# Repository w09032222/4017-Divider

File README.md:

# 4017-Divider

A simple 2hp clock divider module inspired by the 4017 ic.

Input a clock signal and the other 7 outputs will send out signals which dividing the input's frequency by 2 to 8.

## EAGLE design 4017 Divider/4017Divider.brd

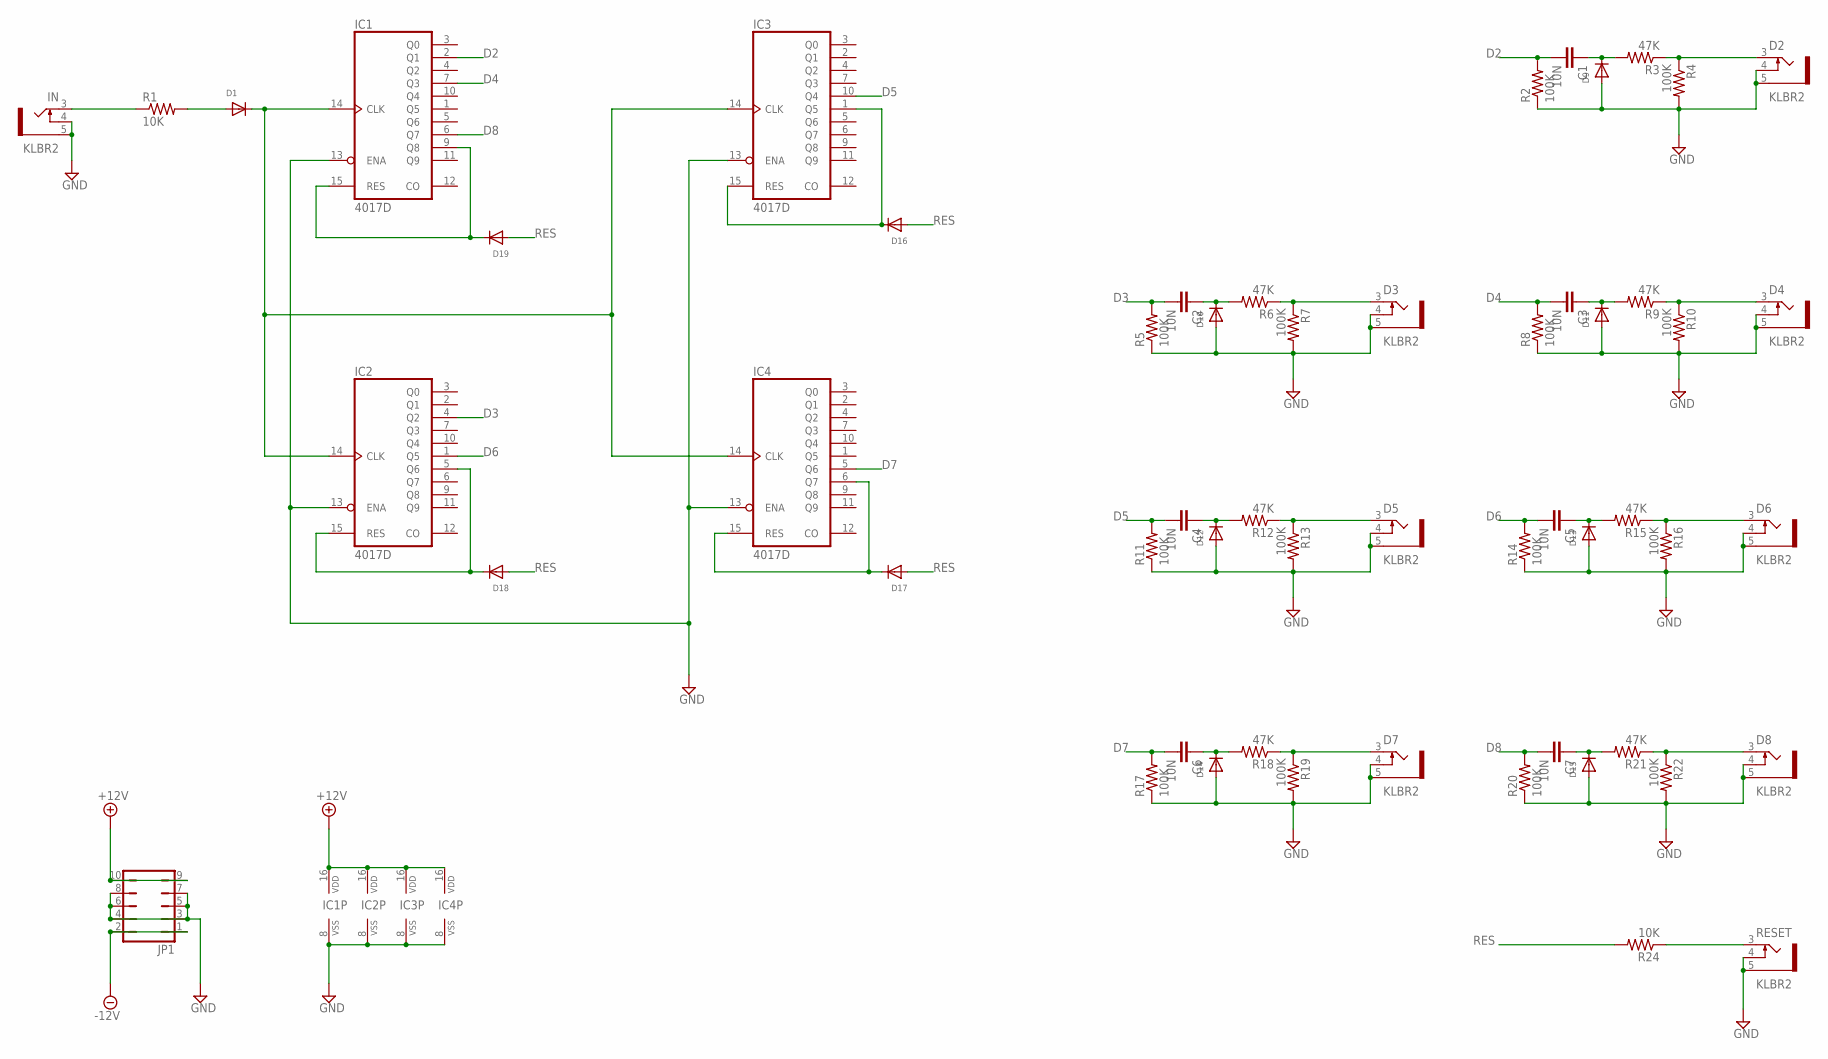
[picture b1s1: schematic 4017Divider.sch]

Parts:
C1, C2, C3, C4, C5, C6, C7: 10N; C0603K
D1, D9, D10, D11, D12, D13, D14, D15, D16, D17, D18, D19: DIODESOD-123; SOD-123
D2, D3, D4, D5, D6, D7, D8: KLBR2
IC1, IC2, IC3, IC4: 4017D; SO16
IN: KLBR2
JP1: JP5Q
R1, R24: 10K; R0603
R2, R4, R5, R7, R8, R10, R11, R13, R14, R16, R17, R19, R20, R22: 100K; R0603
R3, R6, R9, R12, R15, R18, R21: 47K; R0603
RESET: KLBR2

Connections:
+12V: IC1.16 (VDD), IC2.16 (VDD), IC3.16 (VDD), IC4.16 (VDD), JP1.9, JP1.10
-12V: JP1.1, JP1.2
D2: C1.2, IC1.2 (Q1), R2.2
D3: C2.2, IC2.4 (Q2), R5.2
D4: C3.2, IC1.7 (Q3), R8.2
D5: C4.2, IC3.10 (Q4), R11.2
D6: C5.2, IC2.1 (Q5), R14.2
D7: C6.2, IC4.5 (Q6), R17.2
D8: C7.2, IC1.6 (Q7), R20.2
GND: D2.4, D2.5, D3.4, D3.5, D4.4, D4.5, D5.4, D5.5, D6.4, D6.5, D7.4, D7.5, D8.4, D8.5, D9.A, D10.A, D11.A, D12.A, D13.A, D14.A, D15.A, IC1.8 (VSS), IC1.13 (ENA), IC2.8 (VSS), IC2.13 (ENA), IC3.8 (VSS), IC3.13 (ENA), IC4.8 (VSS), IC4.13 (ENA), IN.4, IN.5, JP1.3, JP1.4, JP1.5, JP1.6, JP1.7, JP1.8, R2.1, R4.2, R5.1, R7.2, R8.1, R10.2, R11.1, R13.2, R14.1, R16.2, R17.1, R19.2, R20.1, R22.2, RESET.4, RESET.5
unnamed: D1.A, R1.2
unnamed: D1.C, IC1.14 (CLK), IC2.14 (CLK), IC3.14 (CLK), IC4.14 (CLK)
unnamed: C2.1, D10.C, R6.2
unnamed: IN.3, R1.1
unnamed: C1.1, D9.C, R3.2
unnamed: D2.3, R3.1, R4.1
unnamed: D3.3, R6.1, R7.1
unnamed: C4.1, D12.C, R12.2
unnamed: C3.1, D11.C, R9.2
unnamed: D4.3, R9.1, R10.1
unnamed: D5.3, R12.1, R13.1
unnamed: C5.1, D13.C, R15.2
unnamed: D6.3, R15.1, R16.1
unnamed: C6.1, D14.C, R18.2
unnamed: D7.3, R18.1, R19.1
unnamed: C7.1, D15.C, R21.2
unnamed: D8.3, R21.1, R22.1
unnamed: D18.C, IC2.5 (Q6), IC2.15 (RES)
unnamed: R24.1, RESET.3
unnamed: D17.C, IC4.6 (Q7), IC4.15 (RES)
unnamed: D19.C, IC1.9 (Q8), IC1.15 (RES)
unnamed: D16.C, IC3.1 (Q5), IC3.15 (RES)
RES: D16.A, D17.A, D18.A, D19.A, R24.2

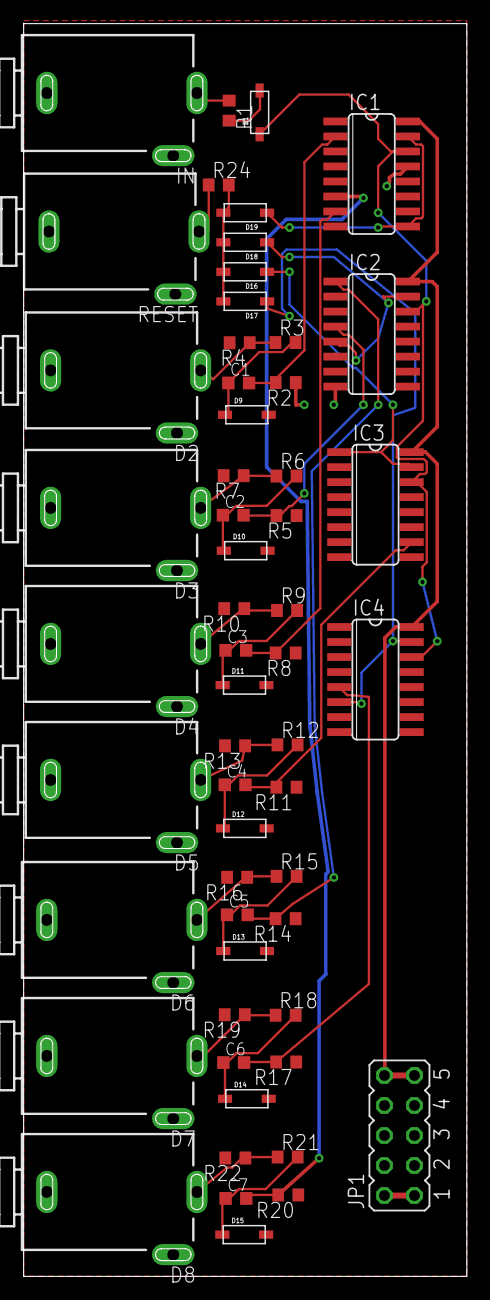
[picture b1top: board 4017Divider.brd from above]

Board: 2 copper layers, 37.5 x 106.0 mm, 56 parts (0 on the bottom side), 33 nets.
